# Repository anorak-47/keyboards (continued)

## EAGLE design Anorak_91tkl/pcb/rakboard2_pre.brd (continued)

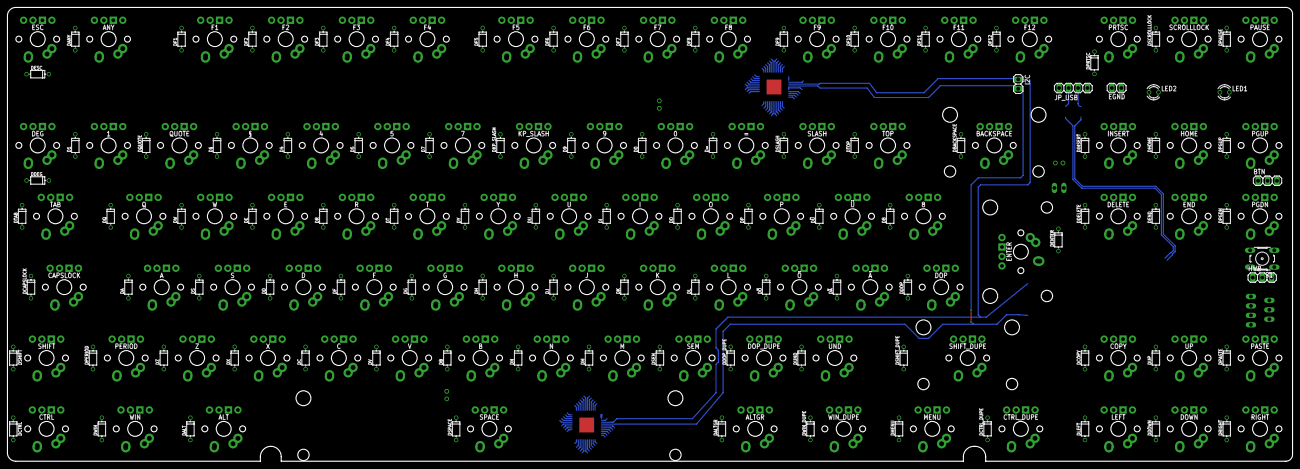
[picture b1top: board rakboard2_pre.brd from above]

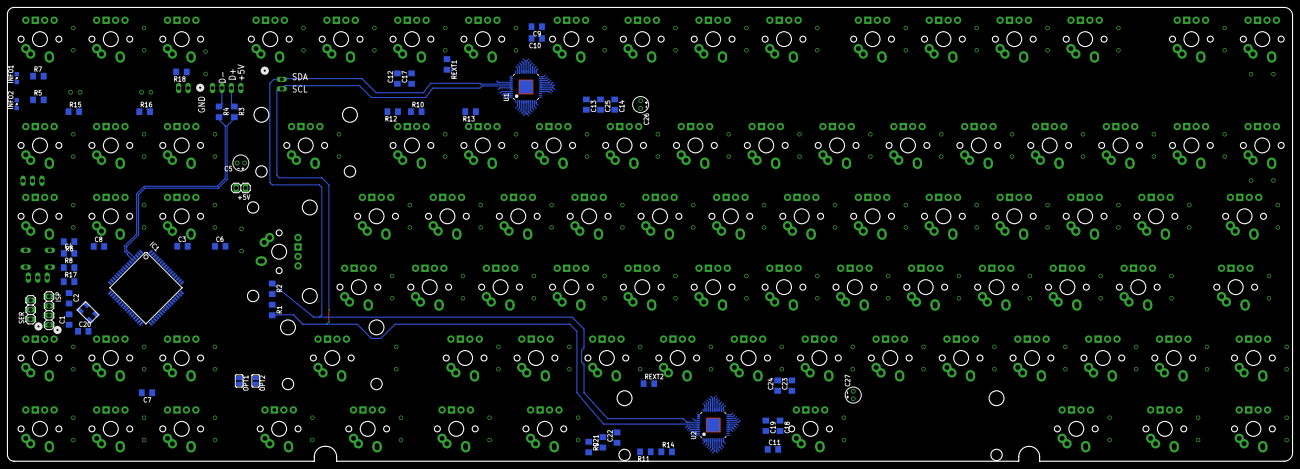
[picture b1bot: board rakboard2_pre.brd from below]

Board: 2 copper layers, 345.5 x 122.0 mm, 246 parts (56 on the bottom side), 205 nets.

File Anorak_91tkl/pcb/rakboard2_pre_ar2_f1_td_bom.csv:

"Qty";"Value";"Device";"Package";"Parts";"Description";"MF";"MPN";"OC_FARNELL";"OC_NEWARK";
"1";"";"10-XX";"B3F-10XX";"S1";"OMRON SWITCH";"";"B3F-1000";"176432";"36M3542";
"91";"";"DIODE'1N4148'";"DO-35";"D0, D1, D4, D5, D7, D8, D9, D=, DA, DALT, DALTGR, DANY, DB, DBACKSPACE, DC, DCAPSLOCK, DCOPY, DCTRL, DCTRL_DUPE, DD, DDEG, DDELETE, DDOP, DDOP_DUPE, DDOWN, DE, DEND, DENTER, DESC, DF, DF1, DF2, DF3, DF4, DF5, DF6, DF7, DF8, DF9, DF10, DF11, DF12, DG, DH, DHOME, DI, DINSERT, DJ, DK, DKP_SLASH, DL, DLEFT, DM, DMENU, DN, DO, DP, DPASTE, DPAUSE, DPERIOD, DPGDN, DPGUP, DPRTSC, DQ, DQUOTE, DR, DRIGHT, DS, DSCROLLLOCK, DSEM, DSHIFT, DSHIFT_DUPE, DSLASH, DSPACE, DT, DTAB, DTOP, DU, DUND, DUP, DV, DW, DWIN, DWIN_DUPE, DX, DY, DZ, D§, DÄ, DÖ, DÜ";"";"";"";"";"";
"2";"";"IS31FL3733";"LQFP48_7X7";"U1, U2";"310080003";"";"";"";"";
"2";"";"LED3MM";"LED3MM";"LED1, LED2";"LED";"";"";"";"";
"2";"";"LEDSML0805";"SML0805";"INFO1, INFO2";"LED";"";"";"";"";
"5";"0,1uF";"C-EUC1206";"C1206";"C10, C13, C19, C22, C24";"CAPACITOR, European symbol";"";"";"";"";
"6";"0,47uF";"C-EUC1206";"C1206";"C9, C12, C18, C21, C23, C25";"CAPACITOR, European symbol";"";"";"";"";
"8";"100k";"R-EU_R1206";"R1206";"R8, R9, R10, R11, R12, R13, R14, R17";"RESISTOR, European symbol";"";"";"";"";
"5";"100n";"C-EUC1206";"C1206";"C3, C4, C6, C7, C8";"CAPACITOR, European symbol";"";"";"";"";
"1";"100nF";"C-EUC1206";"C1206";"C17";"CAPACITOR, European symbol";"";"";"";"";
"1";"10k";"R-EU_R1206";"R1206";"R6";"RESISTOR, European symbol";"";"";"";"";
"1";"10uF";"CPOL-EUE2-4";"E2-4";"C5";"POLARIZED CAPACITOR, European symbol";"";"";"";"";
"1";"16MHz";"CRYSTALMJ";"MJ";"Q4";"";"";"";"";"";
"1";"1M0";"R-EU_R1206";"R1206";"R18";"RESISTOR, European symbol";"";"";"";"";
"1";"1uF";"C-EUC1206";"C1206";"C2";"CAPACITOR, European symbol";"";"";"";"";
"2";"20k";"R-EU_R1206";"R1206";"REXT1, REXT2";"RESISTOR, European symbol";"";"";"";"";
"2";"22";"R-EU_R1206";"R1206";"R3, R4";"RESISTOR, European symbol";"";"";"";"";
"2";"22pF";"C-EUC1206";"C1206";"C1, C20";"CAPACITOR, European symbol";"";"";"";"";
"2";"22uF";"CPOL-EUE2-4";"E2-4";"C26, C27";"POLARIZED CAPACITOR, European symbol";"";"";"";"";
"4";"270";"R-EU_R1206";"R1206";"R5, R7, R15, R16";"RESISTOR, European symbol";"";"";"";"";
"2";"470nF";"C-EUC1206";"C1206";"C11, C14";"CAPACITOR, European symbol";"";"";"";"";
"2";"4K7";"R-EU_R1206";"R1206";"R1, R2";"RESISTOR, European symbol";"";"";"";"";
"1";"AT90USB1286";"AT90USB-TQFP";"TQFP64";"IC1";"";"";"";"";"";
"1";"ESD";"PINHD-1X2";"1X02";"EGND";"PIN HEADER";"";"";"";"";
"1";"JP1";"PINHD-1X3";"1X03";"BTN";"PIN HEADER";"";"";"";"";
"1";"JP2";"PINHD-1X3";"1X03";"HWB";"PIN HEADER";"";"";"";"";
"1";"JP3";"PINHD-1X3";"1X03";"SER";"PIN HEADER";"";"";"";"";
"1";"JP4";"PINHD-1X4";"1X04";"ISP";"PIN HEADER";"";"";"";"";
"1";"JP5";"PINHD-1X2";"1X02";"I2C";"PIN HEADER";"";"";"";"";
"1";"JP_USB";"PINHD-1X4";"1X04";"JP_USB";"PIN HEADER";"";"";"";"";
"87";"KEYSWITCH-RGBLED-ALPSMX-1U-RGB";"KEYSWITCH-RGBLED-ALPSMX-1U-RGB";"ALPSMX-1U-RGB";"0, 1, 4, 5, 7, 8, 9, =, A, ALT, ALTGR, ANY, B, C, CAPSLOCK, COPY, CTRL, CTRL_DUPE, D, DEG, DELETE, DOP, DOP_DUPE, DOWN, E, END, ESC, F, F1, F2, F3, F4, F5, F6, F7, F8, F9, F10, F11, F12, G, H, HOME, I, INSERT, J, K, KP_SLASH, L, LEFT, M, MENU, N, O, P, PASTE, PAUSE, PERIOD, PGDN, PGUP, PRTSC, Q, QUOTE, R, RIGHT, S, SCROLLLOCK, SEM, SHIFT, SLASH, T, TAB, TOP, U, UND, UP, V, W, WIN, WIN_DUPE, X, Y, Z, §, Ä, Ö, Ü";"";"";"";"";"";
"3";"KEYSWITCH-RGBLED-ALPSMX-2U-RGB";"KEYSWITCH-RGBLED-ALPSMX-2U-RGB";"ALPSMX-2U-RGB";"BACKSPACE, ENTER, SHIFT_DUPE";"";"";"";"";"";
"1";"KEYSWITCH-RGBLED-ALPSMX-6.25U-RGB";"KEYSWITCH-RGBLED-ALPSMX-6.25U-RGB";"ALPSMX-6.25U-RGB";"SPACE";"";"";"";"";"";
"1";"OPT1";"SJ";"SJ";"OPT1";"SMD solder JUMPER";"";"";"";"";
"1";"OPT2";"SJ";"SJ";"OPT2";"SMD solder JUMPER";"";"";"";"";
"1";"PWR";"PINHD-1X2";"1X02";"+5V";"PIN HEADER";"";"";"";"";

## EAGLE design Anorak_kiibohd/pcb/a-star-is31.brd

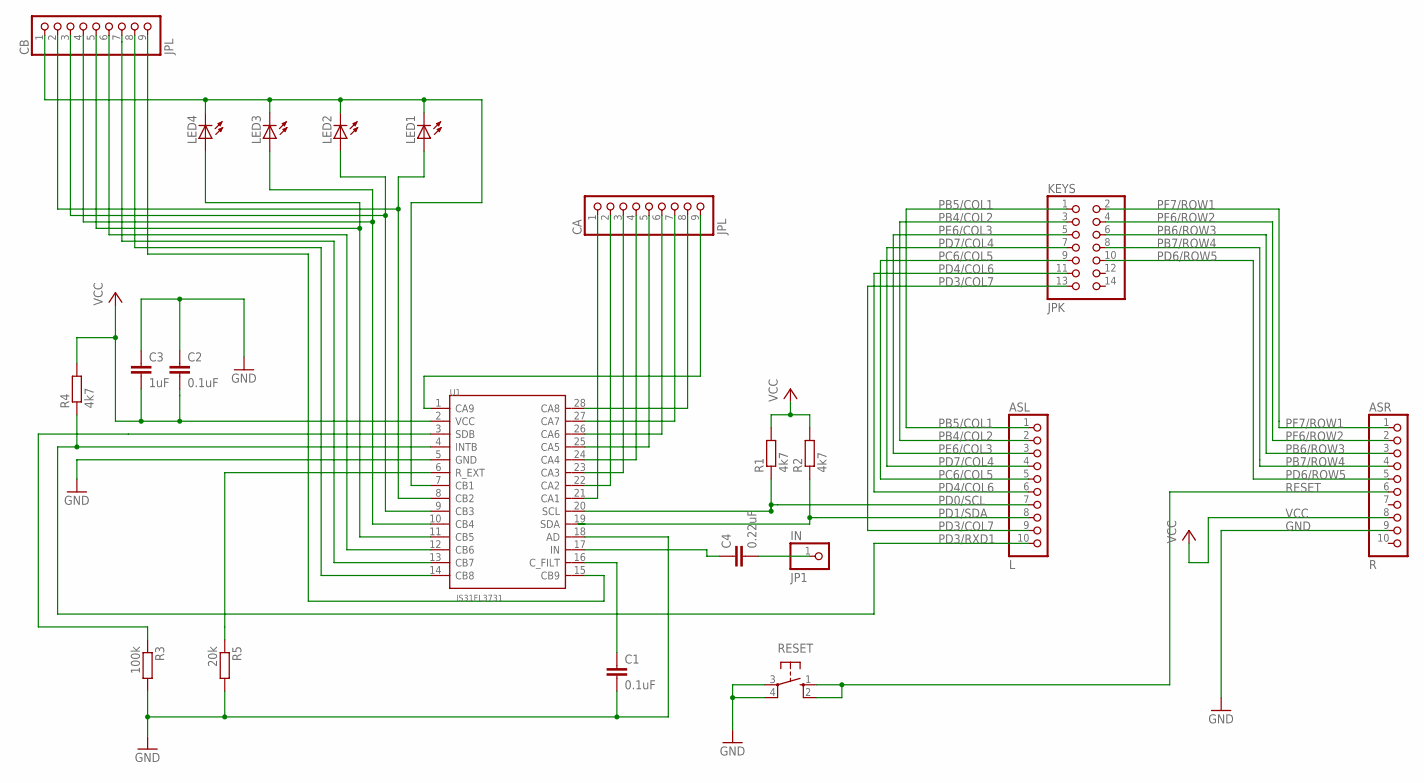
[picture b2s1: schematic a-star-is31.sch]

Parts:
ASL: L; 1X10
ASR: R; 1X10
C1, C2: 0.1uF; C025-025X050
C3: 1uF; C025-025X050
C4: 0.22uF; C025-025X050
CA: JPL; 1X09
CB: JPL; 1X09
IN: JP1; 1X01
KEYS: JPK; 2X07
LED1, LED2, LED3, LED4: LED3MM
R1, R2, R4: 4k7; 0207/10
R3: 100k; 0207/10
R5: 20k; 0207/10
RESET: 10-XX; B3F-10XX
U1: IS31FL3731; SSOP28-0.65-10.2X5.2MM

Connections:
CA8: CA.8, U1.28 (CA8)
CB9: CB.9, U1.15 (CB9)
GND: ASR.9, C1.2, C2.1, C3.1, R3.2, R5.2, RESET.3, RESET.4 (P1), U1.5 (GND), U1.18 (AD)
unnamed: C4.1, U1.17 (IN)
unnamed: C4.2, IN.1
unnamed: R5.1, U1.6 (R_EXT)
unnamed: CA.1, U1.21 (CA1)
unnamed: C1.1, U1.16 (C_FILT)
unnamed: CA.2, U1.22 (CA2)
unnamed: CA.3, U1.23 (CA3)
unnamed: CA.4, U1.24 (CA4)
unnamed: CA.5, U1.25 (CA5)
unnamed: CA.6, U1.26 (CA6)
unnamed: CA.7, U1.27 (CA7)
unnamed: CA.9, U1.1 (CA9)
unnamed: CB.1, LED1.K (C), LED2.K (C), LED3.K (C), LED4.K (C), U1.7 (CB1)
unnamed: CB.2, LED1.A, U1.8 (CB2)
unnamed: CB.3, LED2.A, U1.9 (CB3)
unnamed: CB.4, LED3.A, U1.10 (CB4)
unnamed: CB.5, LED4.A, U1.11 (CB5)
unnamed: CB.6, U1.12 (CB6)
unnamed: CB.7, U1.13 (CB7)
unnamed: CB.8, U1.14 (CB8)
PB4/COL2: ASL.2, KEYS.3
PB5/COL1: ASL.1, KEYS.1
PB6/ROW3: ASR.3, KEYS.6
PB7/ROW4: ASR.4, KEYS.8
PC6/COL5: ASL.5, KEYS.9
PD0/SCL: ASL.7, R1.1, U1.20 (SCL)
PD1/SDA: ASL.8, R2.1, U1.19 (SDA)
PD2/RXD1: R3.1, U1.3 (SDB)
PD3/COL7: ASL.9, KEYS.13
PD3/RXD1: ASL.10, R4.1, U1.4 (INTB)
PD4/COL6: ASL.6, KEYS.11
PD6/ROW5: ASR.5, KEYS.10
PD7/COL4: ASL.4, KEYS.7
PE6/COL3: ASL.3, KEYS.5
PF6/ROW2: ASR.2, KEYS.4
PF7/ROW1: ASR.1, KEYS.2
RESET: ASR.6, RESET.1 (S), RESET.2 (S1)
VCC: ASR.8, C2.2, C3.2, R1.2, R2.2, R4.2, U1.2 (VCC)

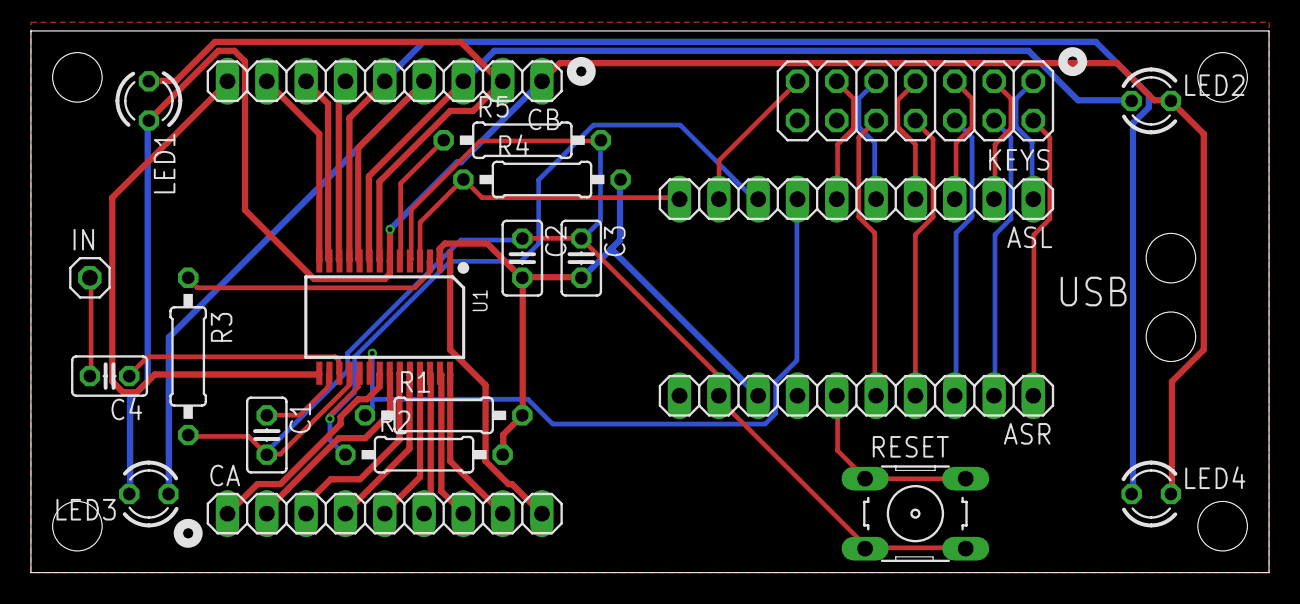
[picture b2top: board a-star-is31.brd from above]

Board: 2 copper layers, 80.0 x 35.0 mm, 21 parts (0 on the bottom side), 41 nets.

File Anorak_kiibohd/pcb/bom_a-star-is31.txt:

Stückliste exportiert aus /home/wenk/eagle/Keyboard/anorak_kiibohd/a-star-is31.sch am 04.03.16 18:20

Part  Value      Device             Package                Description                MF MPN          OC_FARNELL OC_NEWARK VALUE     
ASL   L          PINHD-1X10         1X10                   PIN HEADER                                                                
ASR   R          PINHD-1X10         1X10                   PIN HEADER                                                                
C1    0.1uF      C-EU025-025X050    C025-025X050           CAPACITOR, European symbol                                                
C2    0.1uF      C-EU025-025X050    C025-025X050           CAPACITOR, European symbol                                                
C3    1uF        C-EU025-025X050    C025-025X050           CAPACITOR, European symbol                                                
C4    0.22uF     C-EU025-025X050    C025-025X050           CAPACITOR, European symbol                                                
CA    JPL        PINHD-1X9          1X09                   PIN HEADER                                                                
CB    JPL        PINHD-1X9          1X09                   PIN HEADER                                                                
IN    JP1        PINHD-1X1          1X01                   PIN HEADER                                                                
KEYS  JPK        PINHD-2X7          2X07                   PIN HEADER                                                                
LED1             LED3MM             LED3MM                 LED                                                                       
LED2             LED3MM             LED3MM                 LED                                                                       
LED3             LED3MM             LED3MM                 LED                                                                       
LED4             LED3MM             LED3MM                 LED                                                                       
R1    4k7        R-EU_0207/10       0207/10                RESISTOR, European symbol                                                 
R2    4k7        R-EU_0207/10       0207/10                RESISTOR, European symbol                                                 
R3    100k       R-EU_0207/10       0207/10                RESISTOR, European symbol                                                 
R4    4k7        R-EU_0207/10       0207/10                RESISTOR, European symbol                                                 
R5    20k        R-EU_0207/10       0207/10                RESISTOR, European symbol                                                 
RESET            10-XX              B3F-10XX               OMRON SWITCH                  B3F-1000     176432     36M3542             
U1    IS31FL3731 IS31FL3731(SSOP28) SSOP28-0.65-10.2X5.2MM 310080003                     WM8731SEDS/V                      IS31FL3731

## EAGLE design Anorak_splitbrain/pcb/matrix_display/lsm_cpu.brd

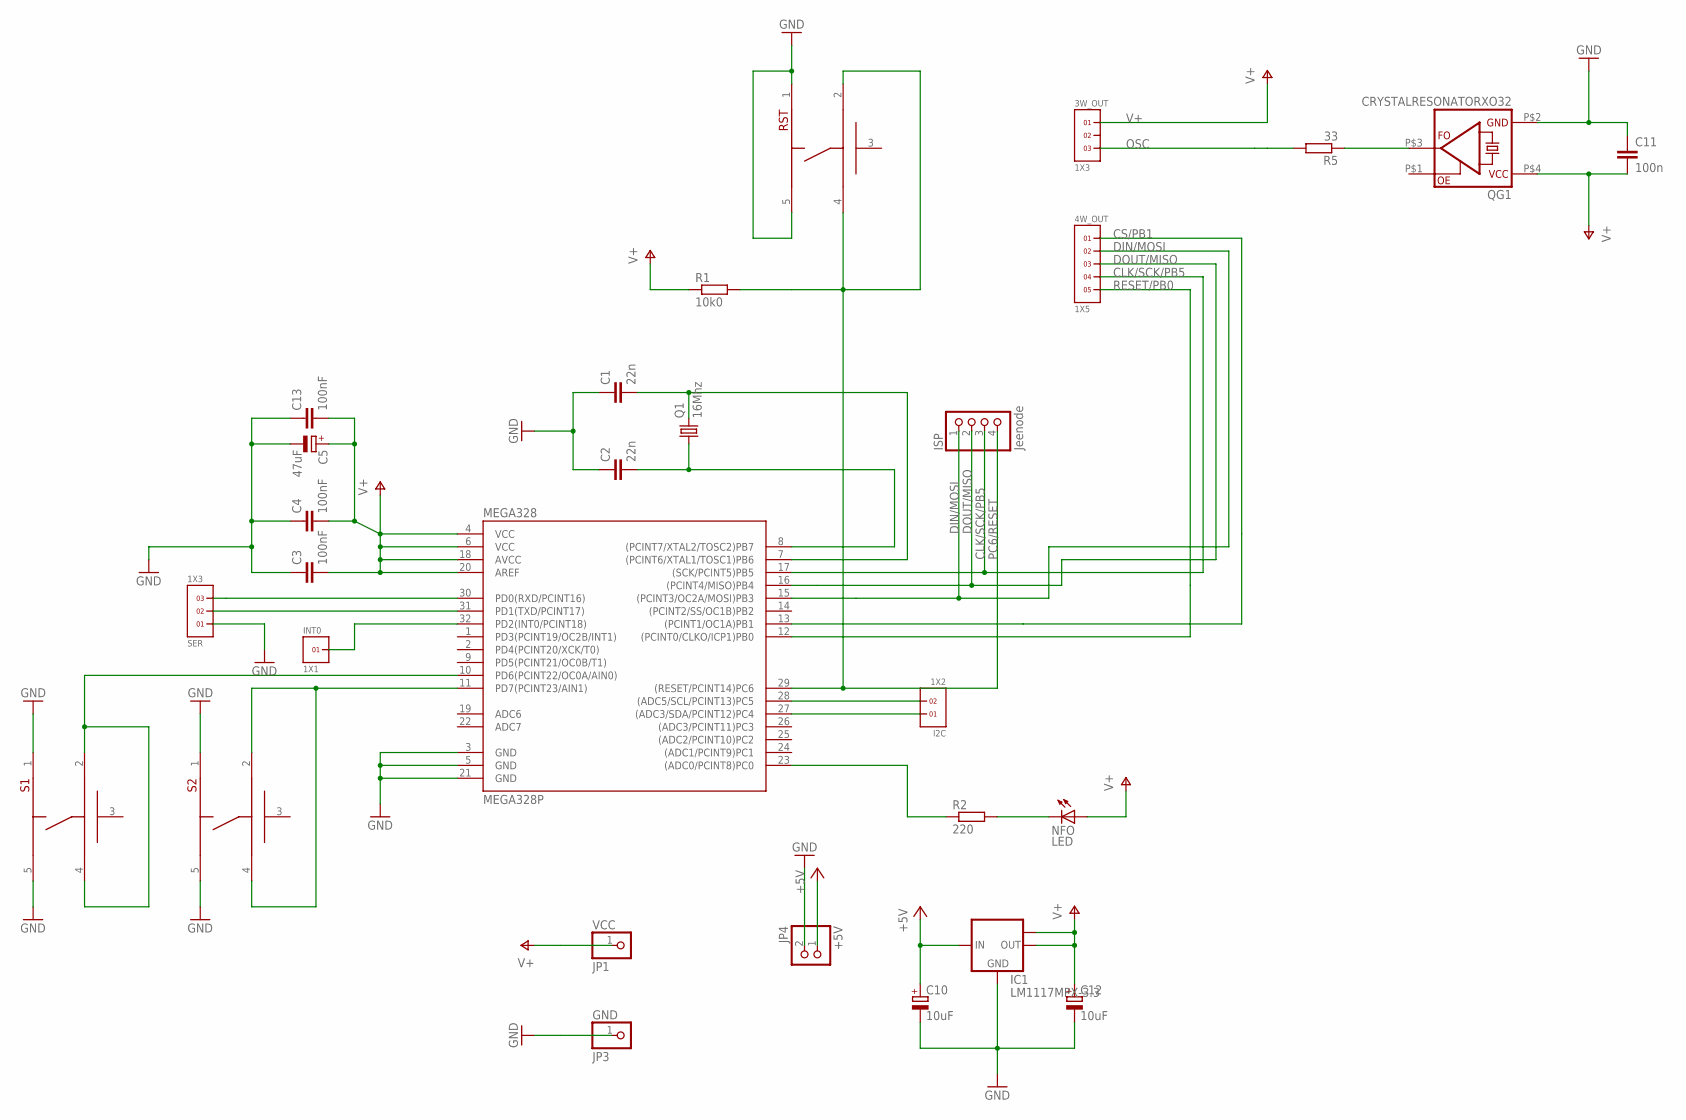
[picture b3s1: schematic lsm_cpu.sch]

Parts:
3W_OUT: 1X3
4W_OUT: 1X5
+5V: JP4; 1X02
C1, C2: 22n; C1206
C3, C4, C13: 100nF; C1206
C5: 47uF; E2-4
C10, C12: 10uF; E2-4
C11: 100n; C1206
GND: JP3; 1X01
I2C: 1X2
IC1: LM1117MPX-3.3; SOT223
INT0: 1X1
ISP: Jeenode; 1X04
MEGA328: MEGA328P; TQFP32-08
NFO: LED; SML1206
Q1: 16Mhz; MT
QG1: CRYSTALRESONATORXO32; XO32
R1: 10k0; R0805
R2: 220; R0805
R5: 33; R0805
RST: KMSXXXG; C&K-KMS-SWITCH
S1, S2: KMSXXXG; C&K-KMS-SWITCH
SER: 1X3
VCC: JP1; 1X01

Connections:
+5V: +5V.1, C10.+, IC1.3 (IN)
CLK/SCK/PB5: 4W_OUT.4, ISP.3, MEGA328.17 ((SCK/PCINT5)PB5)
CS/PB1: 4W_OUT.1, MEGA328.13 ((PCINT1/OC1A)PB1)
DIN/MOSI: 4W_OUT.2, ISP.1, MEGA328.15 ((PCINT3/OC2A/MOSI)PB3)
DOUT/MISO: 4W_OUT.3, ISP.2, MEGA328.16 ((PCINT4/MISO)PB4)
GND: +5V.2, C1.1, C2.1, C3.1, C4.1, C5.-, C10.-, C11.1, C12.-, C13.1, GND.1, IC1.1 (GND), MEGA328.3 (GND), MEGA328.5 (GND), MEGA328.21 (GND), QG1.P$2 (GND), RST.1, RST.5, S1.1, S1.5, S2.1, S2.5, SER.1
unnamed: MEGA328.11 (PD7(PCINT23/AIN1)), S2.2, S2.4
unnamed: MEGA328.10 (PD6(PCINT22/OC0A/AIN0)), S1.2, S1.4
unnamed: C1.2, MEGA328.7 ((PCINT6/XTAL1/TOSC1)PB6), Q1.P3 (2)
unnamed: C2.2, MEGA328.8 ((PCINT7/XTAL2/TOSC2)PB7), Q1.P1 (1)
unnamed: NFO.C, R2.2
unnamed: QG1.P$3 (FO), R5.1
OSC: 3W_OUT.3, R5.2
PC0: MEGA328.23 ((ADC0/PCINT8)PC0), R2.1
PC6/RESET: ISP.4, MEGA328.29 ((RESET/PCINT14)PC6), R1.2, RST.2, RST.4
PD2/INT0/PCINT18: INT0.1, MEGA328.32 (PD2(INT0/PCINT18))
RESET/PB0: 4W_OUT.5, MEGA328.12 ((PCINT0/CLKO/ICP1)PB0)
RXD: MEGA328.30 (PD0(RXD/PCINT16)), SER.3
SCL: I2C.2, MEGA328.28 ((ADC5/SCL/PCINT13)PC5)
SDA: I2C.1, MEGA328.27 ((ADC3/SDA/PCINT12)PC4)
TXD: MEGA328.31 (PD1(TXD/PCINT17)), SER.2
V+: 3W_OUT.1, C3.2, C4.2, C5.+, C11.2, C12.+, C13.2, IC1.2 (OUT), IC1.TAB (OUT1), MEGA328.4 (VCC), MEGA328.6 (VCC), MEGA328.18 (AVCC), MEGA328.20 (AREF), NFO.A, QG1.P$4 (VCC), R1.1, VCC.1

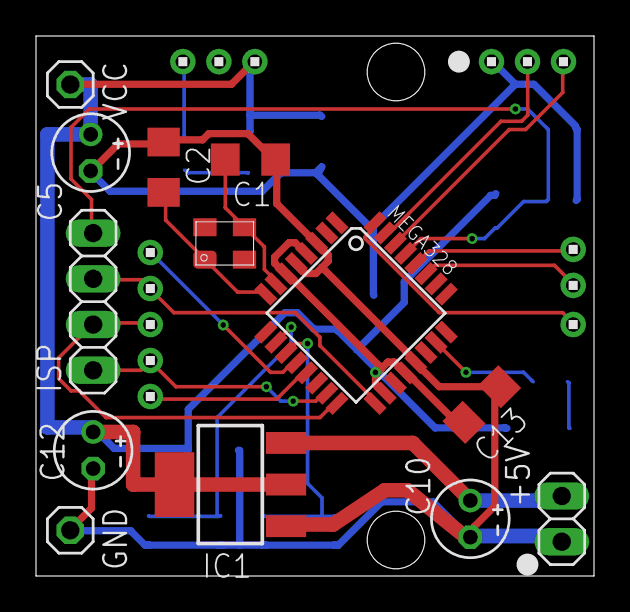
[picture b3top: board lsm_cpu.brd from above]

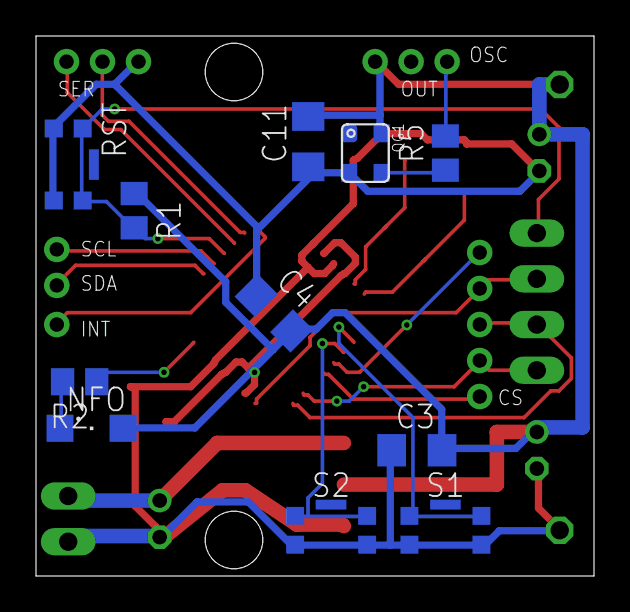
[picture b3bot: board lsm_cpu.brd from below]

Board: 2 copper layers, 31.0 x 30.0 mm, 29 parts (11 on the bottom side), 22 nets.

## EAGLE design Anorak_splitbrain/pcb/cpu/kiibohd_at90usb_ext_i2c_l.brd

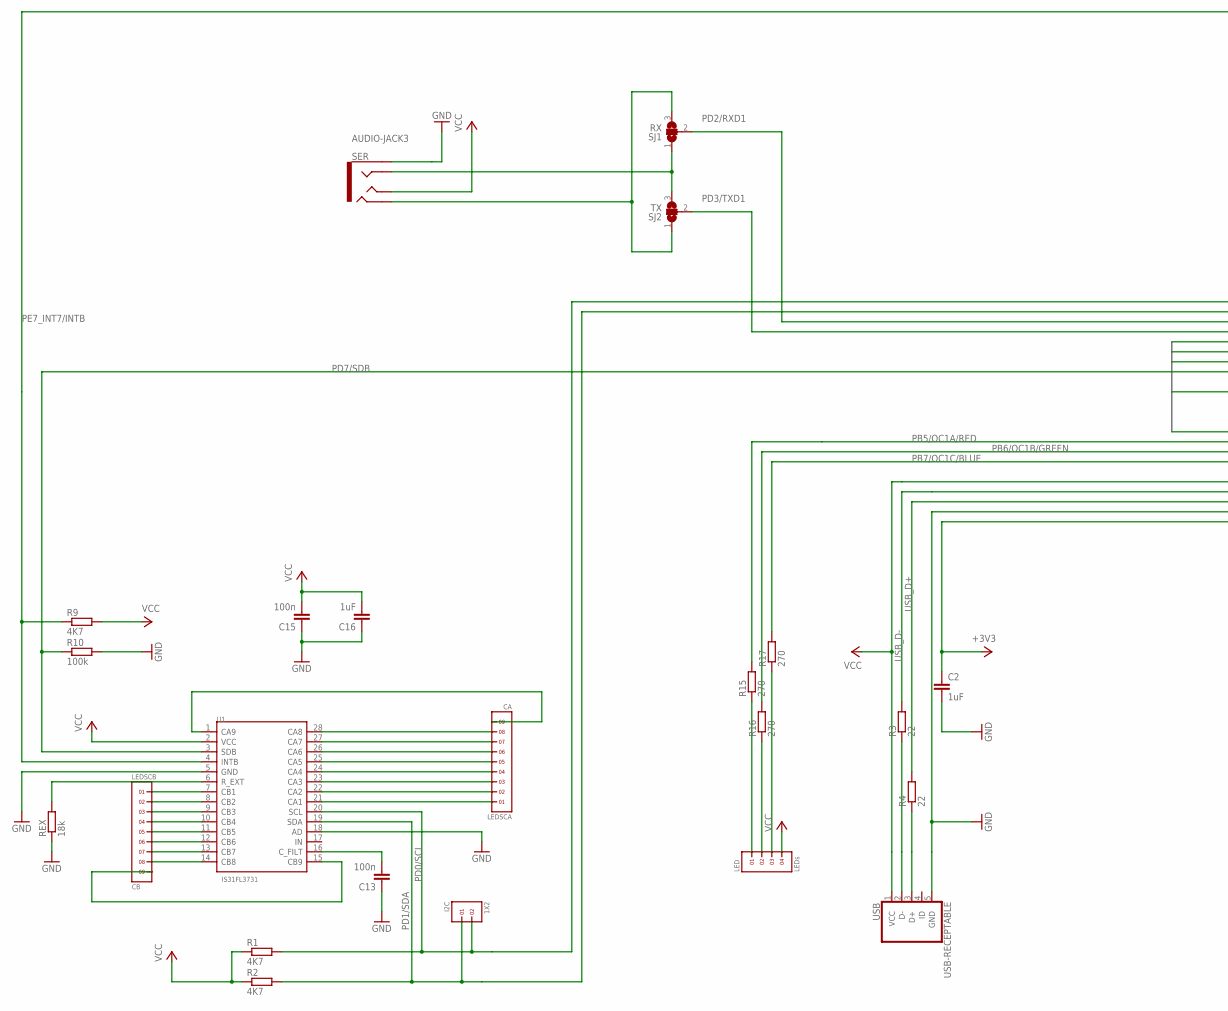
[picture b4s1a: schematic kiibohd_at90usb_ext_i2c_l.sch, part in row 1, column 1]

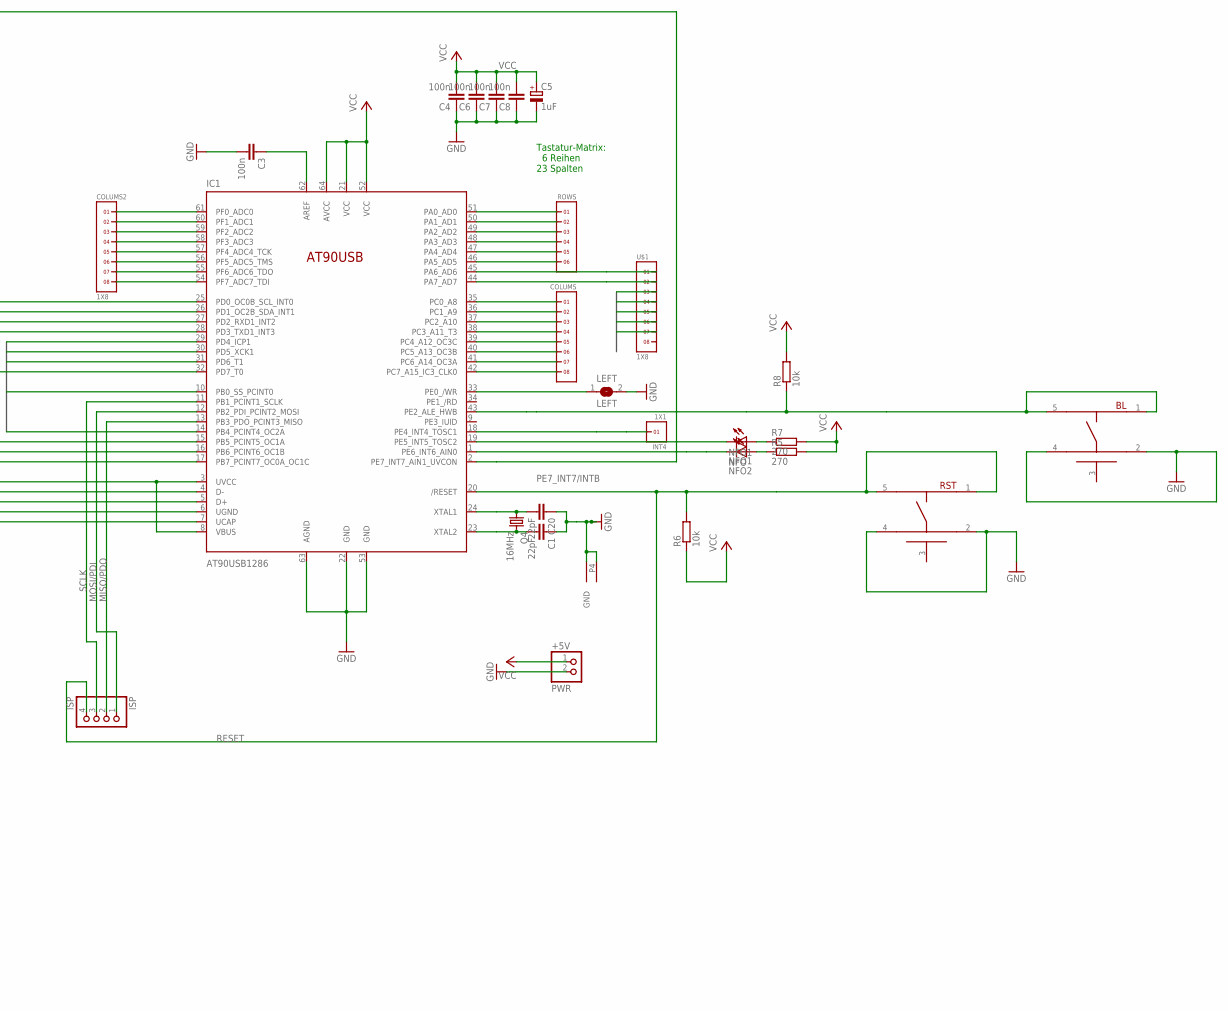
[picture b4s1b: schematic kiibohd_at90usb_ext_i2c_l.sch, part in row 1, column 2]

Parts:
+5V: PWR; 1X02
BL: KMSXXXG; C&K-KMS-SWITCH
C1, C20: 22pF; C1206
C2, C16: 1uF; C1206
C3, C4, C6, C7, C8, C13, C15: 100n; C1206
C5: 1uF; E2-4
COLUMS, COLUMS2: 1X8
I2C: 1X2
IC1: AT90USB1286; TQFP64
INT4: 1X1
ISP: ISP; 1X04
LED: LEDs; 1X4
LEDSCA: CA; 1X9
LEDSCB: CB; 1X9
LEFT: LEFT; SJ
NFO: NFO2; CHIP-LED0805
NFO1: NFO1; CHIP-LED0805
Q4: 16MHz; MJ
R1, R2, R9: 4K7; R1206
R3, R4: 22; R1206
R5, R7, R15, R16, R17: 270; R1206
R6, R8: 10k; R1206
R10: 100k; R1206
REX: 18k; R1206
ROWS: 1X6
RST: KMSXXXG; C&K-KMS-SWITCH
SER: AUDIO-JACK3; AUDIO-JACK-TRRS-SMD
SJ1: RX; SJ_2
SJ2: TX; SJ_2
U1: IS31FL3731; SSOP28-0.65-10.2X5.2MM
U$1: 1X8
USB: USB-RECEPTABLE; FCI-10103594-0001LF

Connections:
+3V3: C2.1, IC1.7 (UCAP)
COL1/PC0: COLUMS.1, IC1.35 (PC0_A8)
COL2/PC1: COLUMS.2, IC1.36 (PC1_A9)
COL3: COLUMS.3, IC1.37 (PC2_A10)
COL4: COLUMS.4, IC1.38 (PC3_A11_T3)
COL5: COLUMS.5, IC1.39 (PC4_A12_OC3C)
COL6: COLUMS.6, IC1.40 (PC5_A13_OC3B)
COL8/PF0: COLUMS2.1, IC1.61 (PF0_ADC0)
COL17/PA6: IC1.45 (PA6_AD6), U$1.1
GND: +5V.2, BL.2, BL.4, C1.1, C2.2, C3.2, C4.1, C5.-, C6.1, C7.1, C8.1, C13.1, C15.1, C16.1, C20.1, IC1.6 (UGND), IC1.22 (GND), IC1.53 (GND), IC1.63 (AGND), LEFT.2, Q4.P2 (GND), Q4.P4 (GND1), R10.2, REX.1, RST.2, RST.4, SER.EARTH, U1.5 (GND), U1.18 (AD), USB.5 (GND)
MISO/PDO: IC1.13 (PB3_PDO_PCINT3_MISO), ISP.2
MOSI/PDI: IC1.12 (PB2_PDI_PCINT2_MOSI), ISP.1
unnamed: LEDSCA.1, U1.21 (CA1)
unnamed: LEDSCA.2, U1.22 (CA2)
unnamed: SER.RING1, SJ1.1, SJ2.3
unnamed: LEDSCA.3, U1.23 (CA3)
unnamed: LEDSCA.4, U1.24 (CA4)
unnamed: LEDSCA.5, U1.25 (CA5)
unnamed: LEDSCA.6, U1.26 (CA6)
unnamed: LEDSCA.7, U1.27 (CA7)
unnamed: LEDSCA.8, U1.28 (CA8)
unnamed: LEDSCA.9, U1.1 (CA9)
unnamed: LEDSCB.1, U1.7 (CB1)
unnamed: LEDSCB.2, U1.8 (CB2)
unnamed: LEDSCB.3, U1.9 (CB3)
unnamed: LEDSCB.4, U1.10 (CB4)
unnamed: LEDSCB.5, U1.11 (CB5)
unnamed: LEDSCB.6, U1.12 (CB6)
unnamed: LEDSCB.7, U1.13 (CB7)
unnamed: LEDSCB.8, U1.14 (CB8)
unnamed: LEDSCB.9, U1.15 (CB9)
unnamed: COLUMS2.2, IC1.60 (PF1_ADC1)
unnamed: COLUMS2.3, IC1.59 (PF2_ADC2)
unnamed: COLUMS2.4, IC1.58 (PF3_ADC3)
unnamed: R3.1, USB.2 (D-)
unnamed: C3.1, IC1.62 (AREF)
unnamed: SER.RING2, SJ1.3, SJ2.1
unnamed: COLUMS2.5, IC1.57 (PF4_ADC4_TCK)
unnamed: COLUMS2.6, IC1.56 (PF5_ADC5_TMS)
unnamed: COLUMS2.7, IC1.55 (PF6_ADC6_TDO)
unnamed: IC1.50 (PA1_AD1), ROWS.2
unnamed: IC1.49 (PA2_AD2), ROWS.3
unnamed: IC1.48 (PA3_AD3), ROWS.4
unnamed: IC1.47 (PA4_AD4), ROWS.5
unnamed: IC1.46 (PA5_AD5), ROWS.6
unnamed: COLUMS2.8, IC1.54 (PF7_ADC7_TDI)
unnamed: IC1.18 (PE4_INT4_TOSC1), INT4.1
unnamed: IC1.44 (PA7_AD7), U$1.2
unnamed: IC1.33 (PE0_/WR), LEFT.1
unnamed: IC1.19 (PE5_INT5_TOSC2), NFO1.C
unnamed: NFO1.A, R7.1
unnamed: NFO.A, R5.1
unnamed: R4.1, USB.3 (D+)
unnamed: IC1.1 (PE6_INT6_AIN0), NFO.C
unnamed: COLUMS.7, IC1.41 (PC6_A14_OC3A)
unnamed: COLUMS.8, IC1.42 (PC7_A15_IC3_CLK0)
unnamed: REX.2, U1.6 (R_EXT)
unnamed: C13.2, U1.16 (C_FILT)
unnamed: C1.2, IC1.23 (XTAL2), Q4.P3 (2)
unnamed: C20.2, IC1.24 (XTAL1), Q4.P1 (1)
unnamed: LED.1, R15.1
unnamed: LED.2, R16.1
unnamed: LED.3, R17.1
unnamed: BL.1, BL.5, IC1.43 (PE2_ALE_HWB), R8.1
PB0: IC1.10 (PB0_SS_PCINT0), U$1.6
PB4: IC1.14 (PB4_PCINT4_OC2A), U$1.7
PB5/OC1A/RED: IC1.15 (PB5_PCINT5_OC1A), R15.2
PB6/OC1B/GREEN: IC1.16 (PB6_PCINT6_OC1B), R16.2
PB7/OC1C/BLUE: IC1.17 (PB7_PCINT7_OC0A_OC1C), R17.2
PD0/SCL: I2C.2, IC1.25 (PD0_OC0B_SCL_INT0), R1.2, U1.20 (SCL)
PD1/SDA: I2C.1, IC1.26 (PD1_OC2B_SDA_INT1), R2.2, U1.19 (SDA)
PD2/RXD1: IC1.27 (PD2_RXD1_INT2), SJ1.2
PD3/TXD1: IC1.28 (PD3_TXD1_INT3), SJ2.2
PD4: IC1.29 (PD4_ICP1), U$1.3
PD5: IC1.30 (PD5_XCK1), U$1.4
PD6: IC1.31 (PD6_T1), U$1.5
PD7/SDB: IC1.32 (PD7_T0), R10.1, U1.3 (SDB)
PE7_INT7/INTB: IC1.2 (PE7_INT7_AIN1_UVCON), R9.1, U1.4 (INTB)
RESET: IC1.20 (/RESET), ISP.4, R6.2, RST.1, RST.5
ROW1: IC1.51 (PA0_AD0), ROWS.1
SCLK: IC1.11 (PB1_PCINT1_SCLK), ISP.3
USB_D+: IC1.5 (D+), R4.2
USB_D-: IC1.4 (D-), R3.2
VCC: +5V.1, C4.2, C5.+, C6.2, C7.2, C8.2, C15.2, C16.2, IC1.3 (UVCC), IC1.8 (VBUS), IC1.21 (VCC), IC1.52 (VCC), IC1.64 (AVCC), LED.4, R1.1, R2.1, R5.2, R6.1, R7.2, R8.2, R9.2, SER.TIP, U1.2 (VCC), USB.1 (VCC)

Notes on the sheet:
Tastatur-Matrix: 6 Reihen 23 Spalten

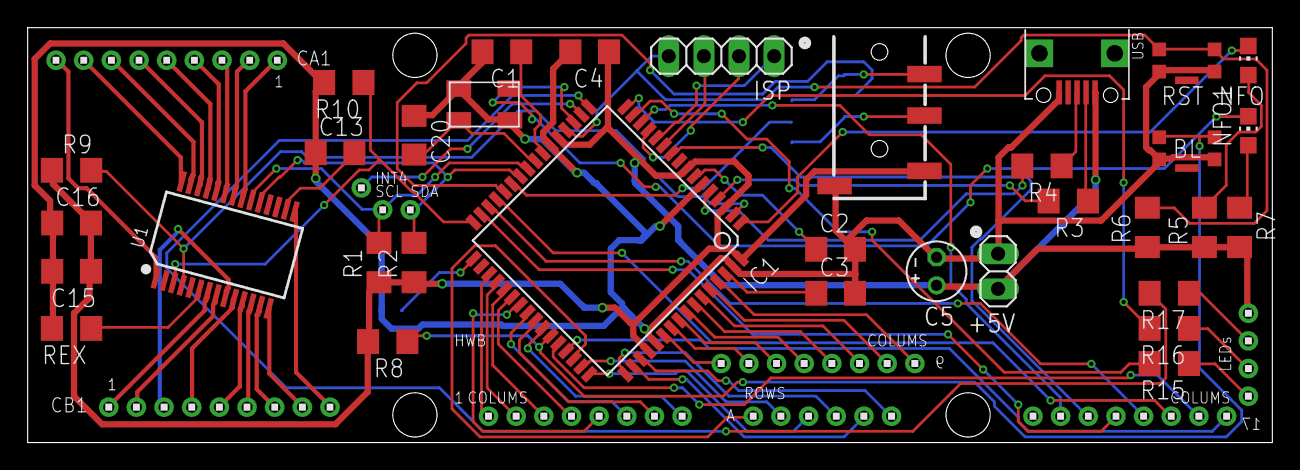
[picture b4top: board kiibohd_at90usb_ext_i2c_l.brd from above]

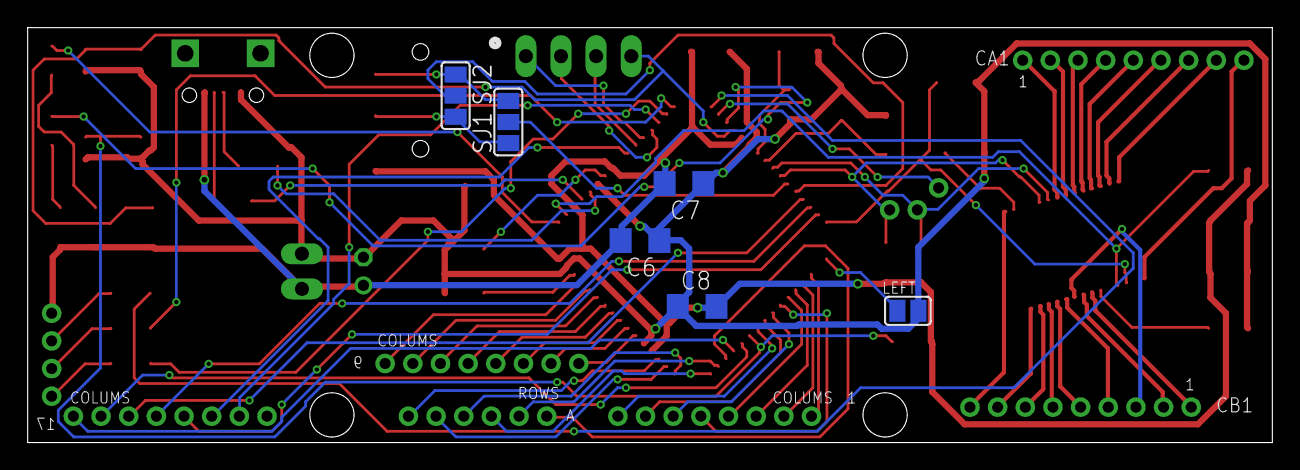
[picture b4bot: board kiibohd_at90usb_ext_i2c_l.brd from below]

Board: 2 copper layers, 90.0 x 30.0 mm, 49 parts (6 on the bottom side), 84 nets.

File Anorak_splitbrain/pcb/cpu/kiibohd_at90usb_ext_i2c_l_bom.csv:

Ord,Best,Qty,Value,De,ice,Package,Parts,Description
x,m,1,AT90USB1286,AT90USB-TQFP,TQFP64,IC1,,
x,m,1,IS31FL3731,IS31FL3731(SSOP28),SSOP28-0.65-10.2X5.2MM,U1,310080003,
x,m,1,USB-RECEPTABLE,USB-RECEPTABLE,FCI-10103594-0001LF,USB,USB Receptable,
,o,1,12,1X10,1X10,COLUMS,,
,o,1,1X2,1X2,1X2,I2C,,
,o,1,SIDE,1X2,1X2,LEFT,,
,o,1,1X3,1X3,1X3,HWB,,
,o,1,LEDs,1X4,1X4,LED,,
,o,1,8,1X8,1X8,ROWS,,
,o,1,CA,1X9,1X9,LEDSCA,,
,o,1,CB,1X9,1X9,LEDSCB,,
,o,1,PWR,PINHD-1X2,1X02,+5V,PIN HEADER,
,o,1,ISP,PINHD-2X3,2X03,SPI,PIN HEADER,
,p,1,AUDIO-JACK3,AUDIO-JACK3,AUDIO-JACK-TRRS-SMD,SER,Audio jack - 3.5mm TRRS ,ariety - two rings.
x,r,4,100n,C-EUC1206,C1206,"C3, C4, C13, C15","CAPACITOR, European symbol",
x,r,2,1uF,C-EUC1206,C1206,"C2, C16","CAPACITOR, European symbol",
x,r,2,22n,C-EUC1206,C1206,"C1, C20","CAPACITOR, European symbol",
x,r,1,1uF,CPOL-EUE2-4,E2-4,C5,"POLARIZED CAPACITOR, European symbol",
x,r,1,16MHz,CRYSTALMJ,MJ,Q4,,
x,r,1,KMSXXXG,KMSXXXG,C&K-KMS-SWITCH,RST,C&K KMS Series,
x,r,1,INFO,LEDCHIP-LED0805,CHIP-LED0805,NFO,LED,
x,r,1,100k,R-EU_R1206,R1206,R10,"RESISTOR, European symbol",
x,r,1,18k,R-EU_R1206,R1206,R_EXT,"RESISTOR, European symbol",
x,r,2,1k0,R-EU_R1206,R1206,"R5, R6","RESISTOR, European symbol",
x,r,2,22,R-EU_R1206,R1206,"R3, R4","RESISTOR, European symbol",
x,r,3,270,R-EU_R1206,R1206,"R15, R16, R17","RESISTOR, European symbol",
x,r,3,4K7,R-EU_R1206,R1206,"R1, R2, R9","RESISTOR, European symbol",

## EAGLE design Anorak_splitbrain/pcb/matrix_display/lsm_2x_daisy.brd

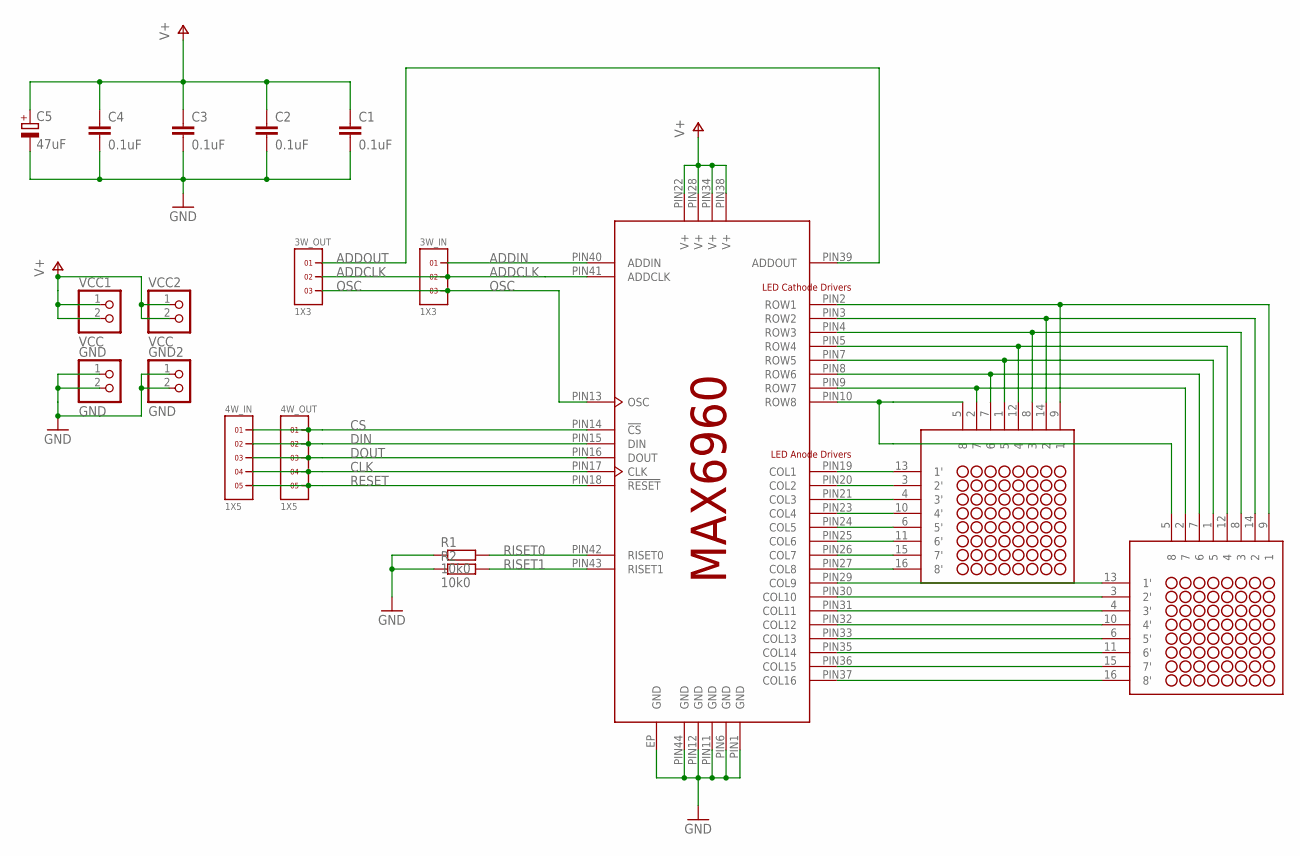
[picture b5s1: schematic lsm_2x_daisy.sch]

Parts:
3W_IN, 3W_OUT: 1X3
4W_IN, 4W_OUT: 1X5
C1, C2, C3, C4: 0.1uF; C0805
C5: 47uF; E2-5
GND, GND2: GND; 1X02
M1, M2: NFM-12881BG-11LILPADS; NFM-12881BG-11-SMALL-LILPADS
MAX6960: MAX6960; 44TQFN-EP
R1, R2: 10k0; R0805
VCC1, VCC2: VCC; 1X02

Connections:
ADDCLK: 3W_IN.2, 3W_OUT.2, MAX6960.PIN41 (ADDCLK)
ADDIN: 3W_IN.1, MAX6960.PIN40 (ADDIN)
ADDOUT: 3W_OUT.1, MAX6960.PIN39 (ADDOUT)
CLK: 4W_IN.4, 4W_OUT.4, MAX6960.PIN17 (CLK)
CS: 4W_IN.1, 4W_OUT.1, MAX6960.PIN14 (!CS)
DIN: 4W_IN.2, 4W_OUT.2, MAX6960.PIN15 (DIN)
DOUT: 4W_IN.3, 4W_OUT.3, MAX6960.PIN16 (DOUT)
GND: C1.2, C2.2, C3.2, C4.2, C5.-, GND.1, GND.2, GND2.1, GND2.2, MAX6960.EP (GND), MAX6960.PIN1 (GND), MAX6960.PIN6 (GND), MAX6960.PIN11 (GND), MAX6960.PIN12 (GND), MAX6960.PIN44 (GND), R1.1, R2.1
unnamed: M1.13 (1'), MAX6960.PIN19 (COL1)
unnamed: M1.3 (2'), MAX6960.PIN20 (COL2)
unnamed: M1.10 (4'), MAX6960.PIN23 (COL4)
unnamed: M1.6 (5'), MAX6960.PIN24 (COL5)
unnamed: M1.11 (6'), MAX6960.PIN25 (COL6)
unnamed: M1.15 (7'), MAX6960.PIN26 (COL7)
unnamed: M1.16 (8'), MAX6960.PIN27 (COL8)
unnamed: M2.13 (1'), MAX6960.PIN29 (COL9)
unnamed: M2.3 (2'), MAX6960.PIN30 (COL10)
unnamed: M2.4 (3'), MAX6960.PIN31 (COL11)
unnamed: M2.10 (4'), MAX6960.PIN32 (COL12)
unnamed: M2.6 (5'), MAX6960.PIN33 (COL13)
unnamed: M2.11 (6'), MAX6960.PIN35 (COL14)
unnamed: M2.15 (7'), MAX6960.PIN36 (COL15)
unnamed: M2.16 (8'), MAX6960.PIN37 (COL16)
unnamed: M1.9 (1), M2.9 (1), MAX6960.PIN2 (ROW1)
unnamed: M1.14 (2), M2.14 (2), MAX6960.PIN3 (ROW2)
unnamed: M1.8 (3), M2.8 (3), MAX6960.PIN4 (ROW3)
unnamed: M1.12 (4), M2.12 (4), MAX6960.PIN5 (ROW4)
unnamed: M1.1 (5), M2.1 (5), MAX6960.PIN7 (ROW5)
unnamed: M1.7 (6), M2.7 (6), MAX6960.PIN8 (ROW6)
unnamed: M1.2 (7), M2.2 (7), MAX6960.PIN9 (ROW7)
unnamed: M1.4 (3'), MAX6960.PIN21 (COL3)
unnamed: M1.5 (8), M2.5 (8), MAX6960.PIN10 (ROW8)
OSC: 3W_IN.3, 3W_OUT.3, MAX6960.PIN13 (OSC)
RESET: 4W_IN.5, 4W_OUT.5, MAX6960.PIN18 (!RESET)
RISET0: MAX6960.PIN42 (RISET0), R1.2
RISET1: MAX6960.PIN43 (RISET1), R2.2
V+: C1.1, C2.1, C3.1, C4.1, C5.+, MAX6960.PIN22 (V+), MAX6960.PIN28 (V+), MAX6960.PIN34 (V+), MAX6960.PIN38 (V+), VCC1.1, VCC1.2, VCC2.1, VCC2.2

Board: 2 copper layers, 18 parts (8 on the bottom side), 37 nets, no tracks yet.

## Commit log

2017-03-21 initial checkin
2017-06-07 More hints for rev 2
2017-06-07 More notes
2017-06-07 Added a newline
2017-07-16 Fixed several cad files for the 91tkl
2017-07-16 Added cad files for the Anorak lefty
